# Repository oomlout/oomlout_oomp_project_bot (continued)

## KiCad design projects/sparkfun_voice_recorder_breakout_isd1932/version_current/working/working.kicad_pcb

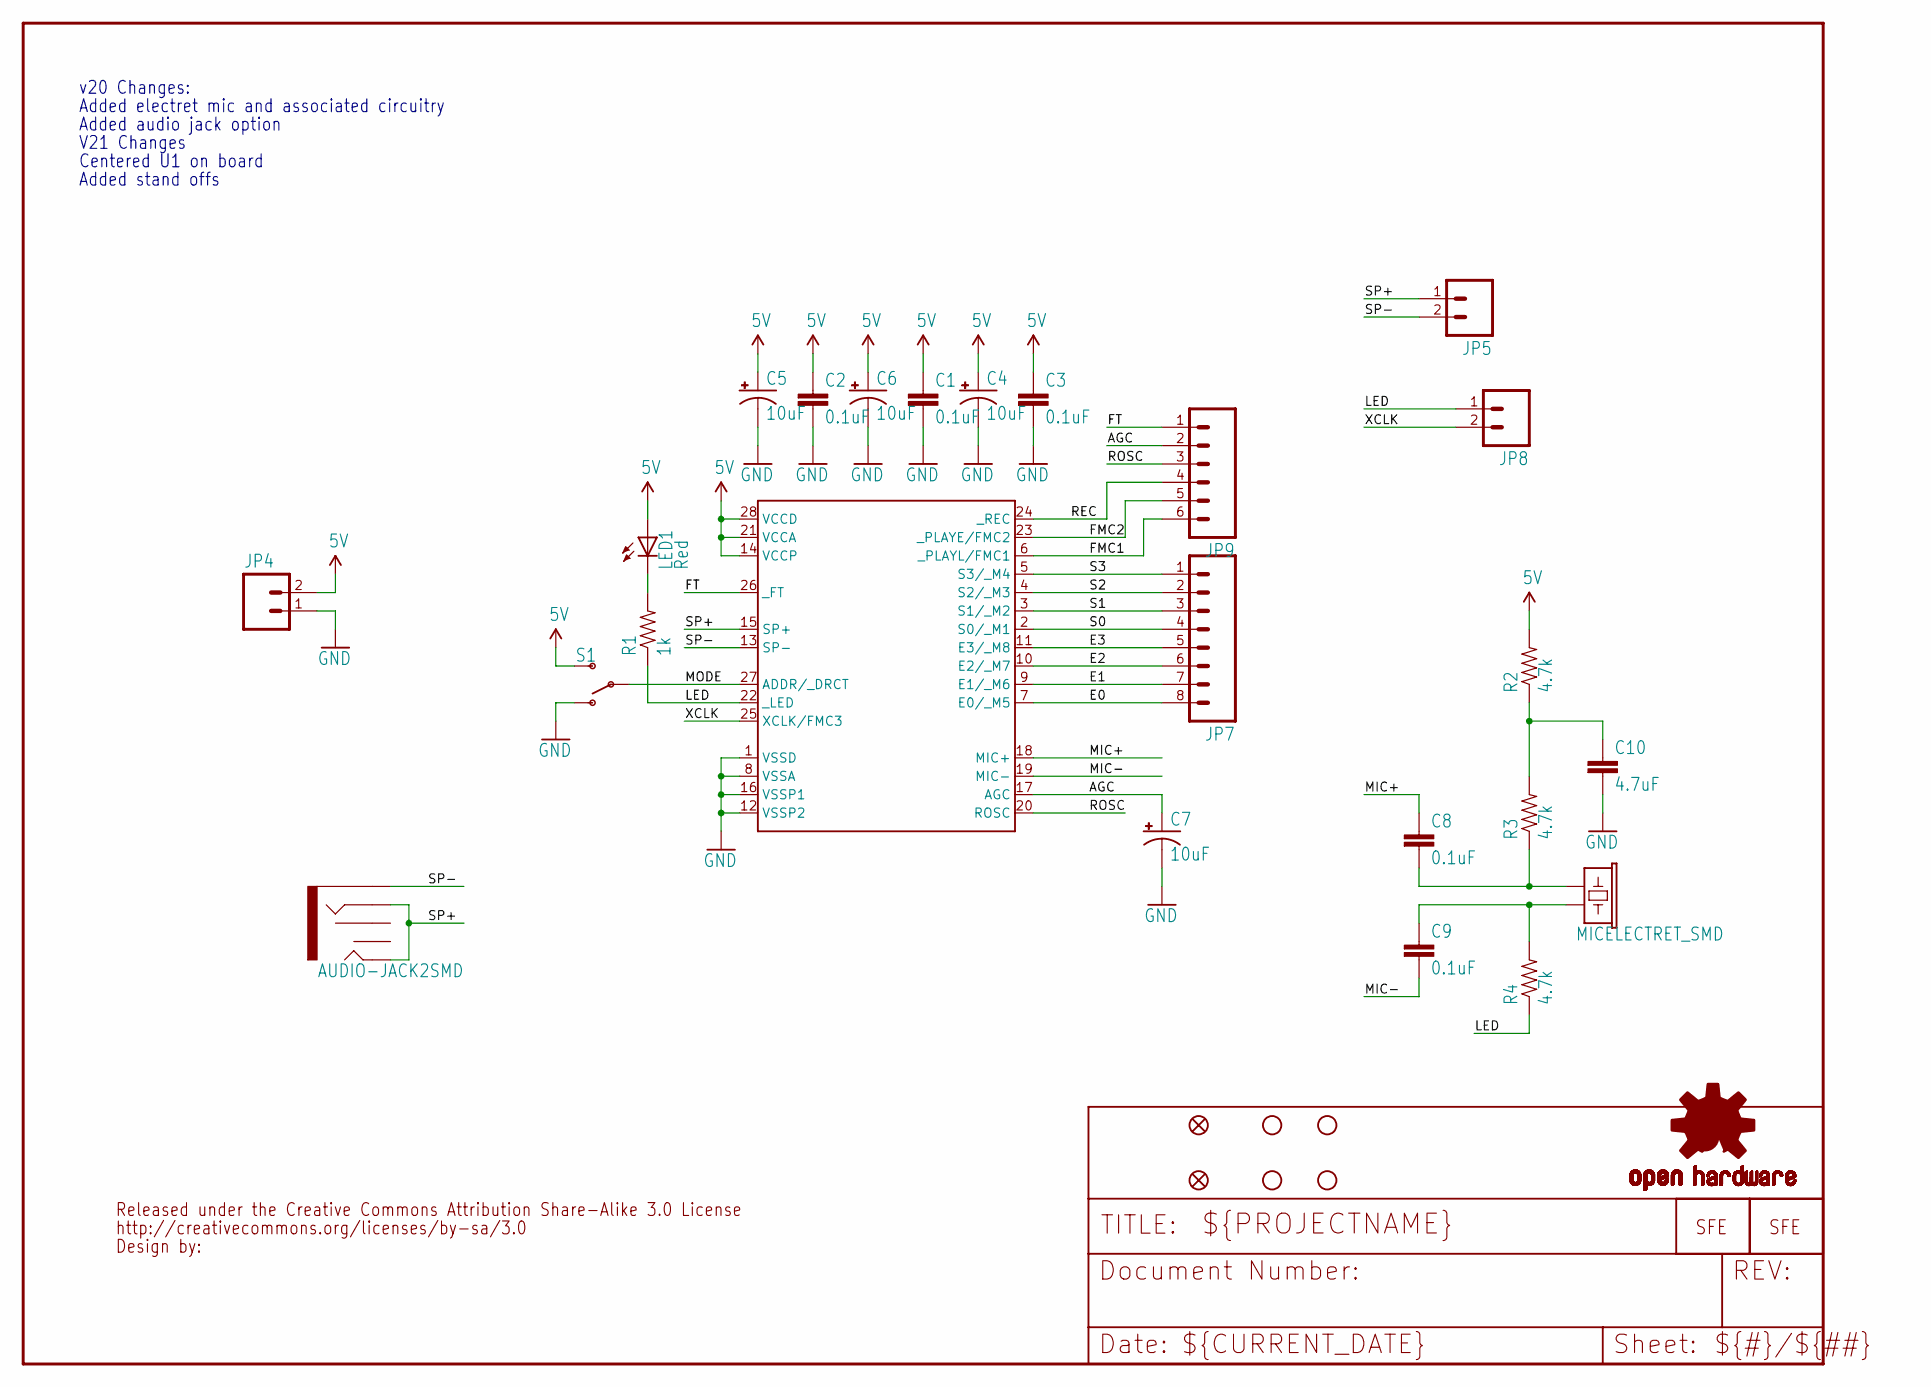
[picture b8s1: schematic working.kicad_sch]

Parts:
C1, C2, C3, C8, C9: 0.1uF; 0603-CAP
C4, C5, C6, C7: 10uF; EIA3216
C10: 4.7uF; 0603-CAP
JP1: LOGO-SFENEW; SFE-NEW-WEBLOGO
JP2, JP3: FIDUCIAL1X2; FIDUCIAL-1X2
JP4, JP5, JP8: M02PTH; 1X02
JP6, JP10, JP11, JP12: STAND-OFF
JP7: M08; 1X08
JP9: M06SIP; 1X06
JP13: LOGO-SFENW2; SFE-NEW-WEB
LED1: Red; LED-0603
R1: 1k; 0603-RES
R2, R3, R4: 4.7k; 0603-RES
S1: SWITCH-SPSTSMD; AYZ0202
U1: ISD1900ISD1932; SO-28W
U2: MICELECTRET_SMD; MIC_ELECTRET_SMD
U3: AUDIO-JACK2SMD; AUDIO-JACK-3.5MM-SMD
U$10: CREATIVE_COMMONS
U$14: OSHW-LOGOL; OSHW-LOGO-L

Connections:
5V: C1.1, C2.1, C3.1, C4.A (+), C5.A (+), C6.A (+), JP4.2, LED1.A, R2.2, S1.3 (S), U1.14 (VCCP), U1.21 (VCCA), U1.28 (VCCD)
AGC: C7.A (+), JP9.2, U1.17 (AGC)
E0: JP7.8, U1.7 (E0/_M5)
E1: JP7.7, U1.9 (E1/_M6)
E2: JP7.6, U1.10 (E2/_M7)
E3: JP7.5, U1.11 (E3/_M8)
FMC1: JP9.6, U1.6 (_PLAYL/FMC1)
FMC2: JP9.5, U1.23 (_PLAYE/FMC2)
FT: JP9.1, U1.26 (_FT)
GND: C1.2, C2.2, C3.2, C4.C (-), C5.C (-), C6.C (-), C7.C (-), C10.2, JP4.1, S1.1 (O), U1.1 (VSSD), U1.8 (VSSA), U1.12 (VSSP2), U1.16 (VSSP1)
LED: JP8.1, R1.1, R4.1, U1.22 (_LED)
MIC+: C8.1, U1.18 (MIC+)
MIC-: C9.2, U1.19 (MIC-)
MODE: S1.2, U1.27 (ADDR/_DRCT)
unnamed: LED1.C, R1.2
unnamed: C8.2, R3.1, U2.1
unnamed: C9.1, R4.2, U2.2
unnamed: C10.1, R2.1, R3.2
REC: JP9.4, U1.24 (_REC)
ROSC: JP9.3, U1.20 (ROSC)
S0: JP7.4, U1.2 (S0/_M1)
S1: JP7.3, U1.3 (S1/_M2)
S2: JP7.2, U1.4 (S2/_M3)
S3: JP7.1, U1.5 (S3/_M4)
SP+: JP5.1, U1.15 (SP+), U3.RING, U3.TIP
SP-: JP5.2, U1.13 (SP-), U3.SLEEVE
XCLK: JP8.2, U1.25 (XCLK/FMC3)

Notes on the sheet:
V21 Changes
Centered U1 on board
Added stand offs
Added audio jack option
Added electret mic and associated circuitry
v20 Changes:

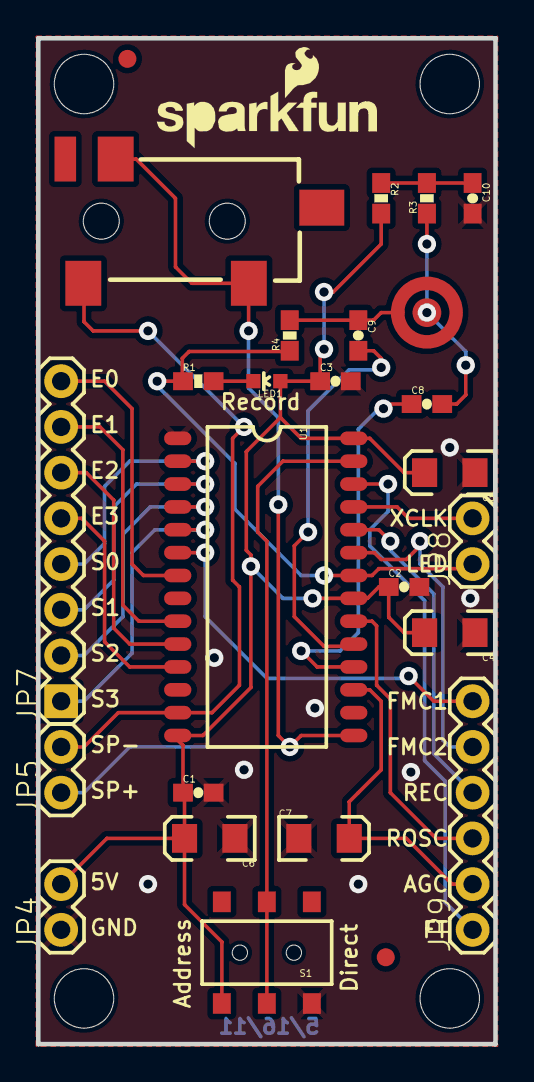
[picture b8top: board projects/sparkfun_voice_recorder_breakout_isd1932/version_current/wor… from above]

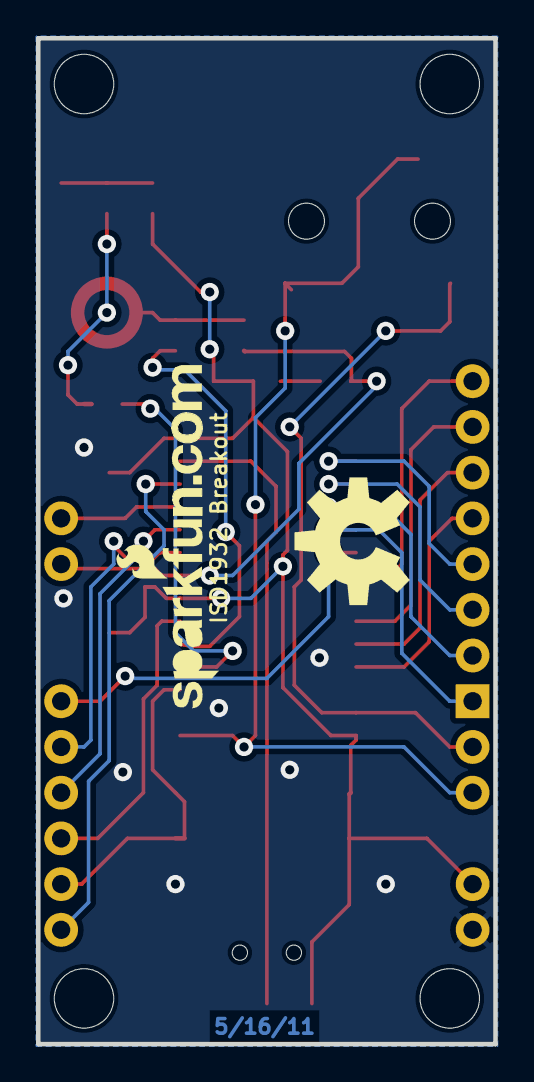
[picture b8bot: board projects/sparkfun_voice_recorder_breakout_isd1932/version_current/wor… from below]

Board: 2 copper layers, 25.4 x 55.9 mm, 35 parts (2 on the bottom side), 27 nets.

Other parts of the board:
U$13: SFE-LOGO-FLAME

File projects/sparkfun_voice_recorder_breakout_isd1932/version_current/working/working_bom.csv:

"Id";"Designator";"Footprint";"Quantity";"Designation";"Supplier and ref";
1;"S1";"AYZ0202";1;"";;;
2;"C10";"0603-CAP";1;"4.7uF";;;
3;"C8,C3,C9,C1,C2";"0603-CAP";5;"0.1uF";;;
4;"JP5,JP8,JP4";"1X02";3;"";;;
5;"R3,R4,R2";"0603-RES";3;"4.7k";;;
6;"LED1";"LED-0603";1;"Red";;;
7;"JP11,JP10,JP6,JP12";"STAND-OFF";4;"STAND-OFF";;;
8;"JP13";"SFE-NEW-WEB";1;"LOGO-SFENW2";;;
9;"U$13";"SFE-LOGO-FLAME";1;"";;;
10;"JP7";"1X08";1;"";;;
11;"C5,C6,C4,C7";"EIA3216";4;"10uF";;;
12;"U2";"MIC_ELECTRET_SMD";1;"MICELECTRET_SMD";;;
13;"R1";"0603-RES";1;"1k";;;
14;"JP9";"1X06";1;"";;;
15;"U1";"SO-28W";1;"ISD1900ISD1932";;;
16;"JP2,JP3";"FIDUCIAL-1X2";2;"FIDUCIAL1X2";;;
17;"U$10";"CREATIVE_COMMONS";1;"CREATIVE_COMMONS";;;
18;"U3";"AUDIO-JACK-3.5MM-SMD";1;"AUDIO-JACK2SMD";;;
19;"U$14";"OSHW-LOGO-L";1;"OSHW-LOGOL";;;
20;"JP1";"SFE-NEW-WEBLOGO";1;"LOGO-SFENEW";;;
